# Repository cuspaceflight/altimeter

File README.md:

# CUSF Altimeter
### This project is a barebones altimeter for use in the freshers rocket challenge. The below instructions are specific to Linux systems only.

## Setting up the Repositiory

1. Setup the repository using the following commands:
```
$ git clone https://github.com/cuspaceflight/altimeter.git
$ cd altimeter
$ git submodule update --init
$ cd ChibiOS
$ git checkout stable_16.1.x
```
2. To succesfully compile firmware you will need to install gcc:
```
$ sudo apt-get install gcc-arm-none-eabi
```
3. Test the installation by compiling the firmware template:
```
$ cd ../firmware
$ make
```

## Analysing Log Files

1. Copy the file "log_0000x.bin" you wish to decode into the altimeter/logs directory

2. From the terminal run:
```
$ python3 log_file_parser.py log_0000x.bin
```

The output will print directly to the terminal window.

## Making Firmware Changes

This will be explained in depth in the sessions, however the files which you will want to modify (status.c, measurements.c and logging.c) can be found in the altimeter/firmware directory.

Compile using the command:
``` 
$ make
```
If successful something similar to the below should appear in the terminal window:

```
...
Compiling testbmk.c
Compiling main.c
Compiling ms5611.c
Compiling measure.c
Compiling status.c
Compiling microsd.c
Compiling logging.c
Linking build/altimeter.elf
Creating build/altimeter.bin
Creating build/altimeter.hex
Creating build/altimeter.dmp
Creating build/altimeter.list

   text	   data	    bss	    dec	    hex	filename
  43900	   8896	 122628	 175424	  2ad40	build/altimeter.elf

Done
```

### References

ChibiOs - http://www.chibios.org/dokuwiki/doku.php?id=chibios:documentation:start

GDB - https://github.com/blacksphere/blackmagic/wiki/Useful-GDB-commands

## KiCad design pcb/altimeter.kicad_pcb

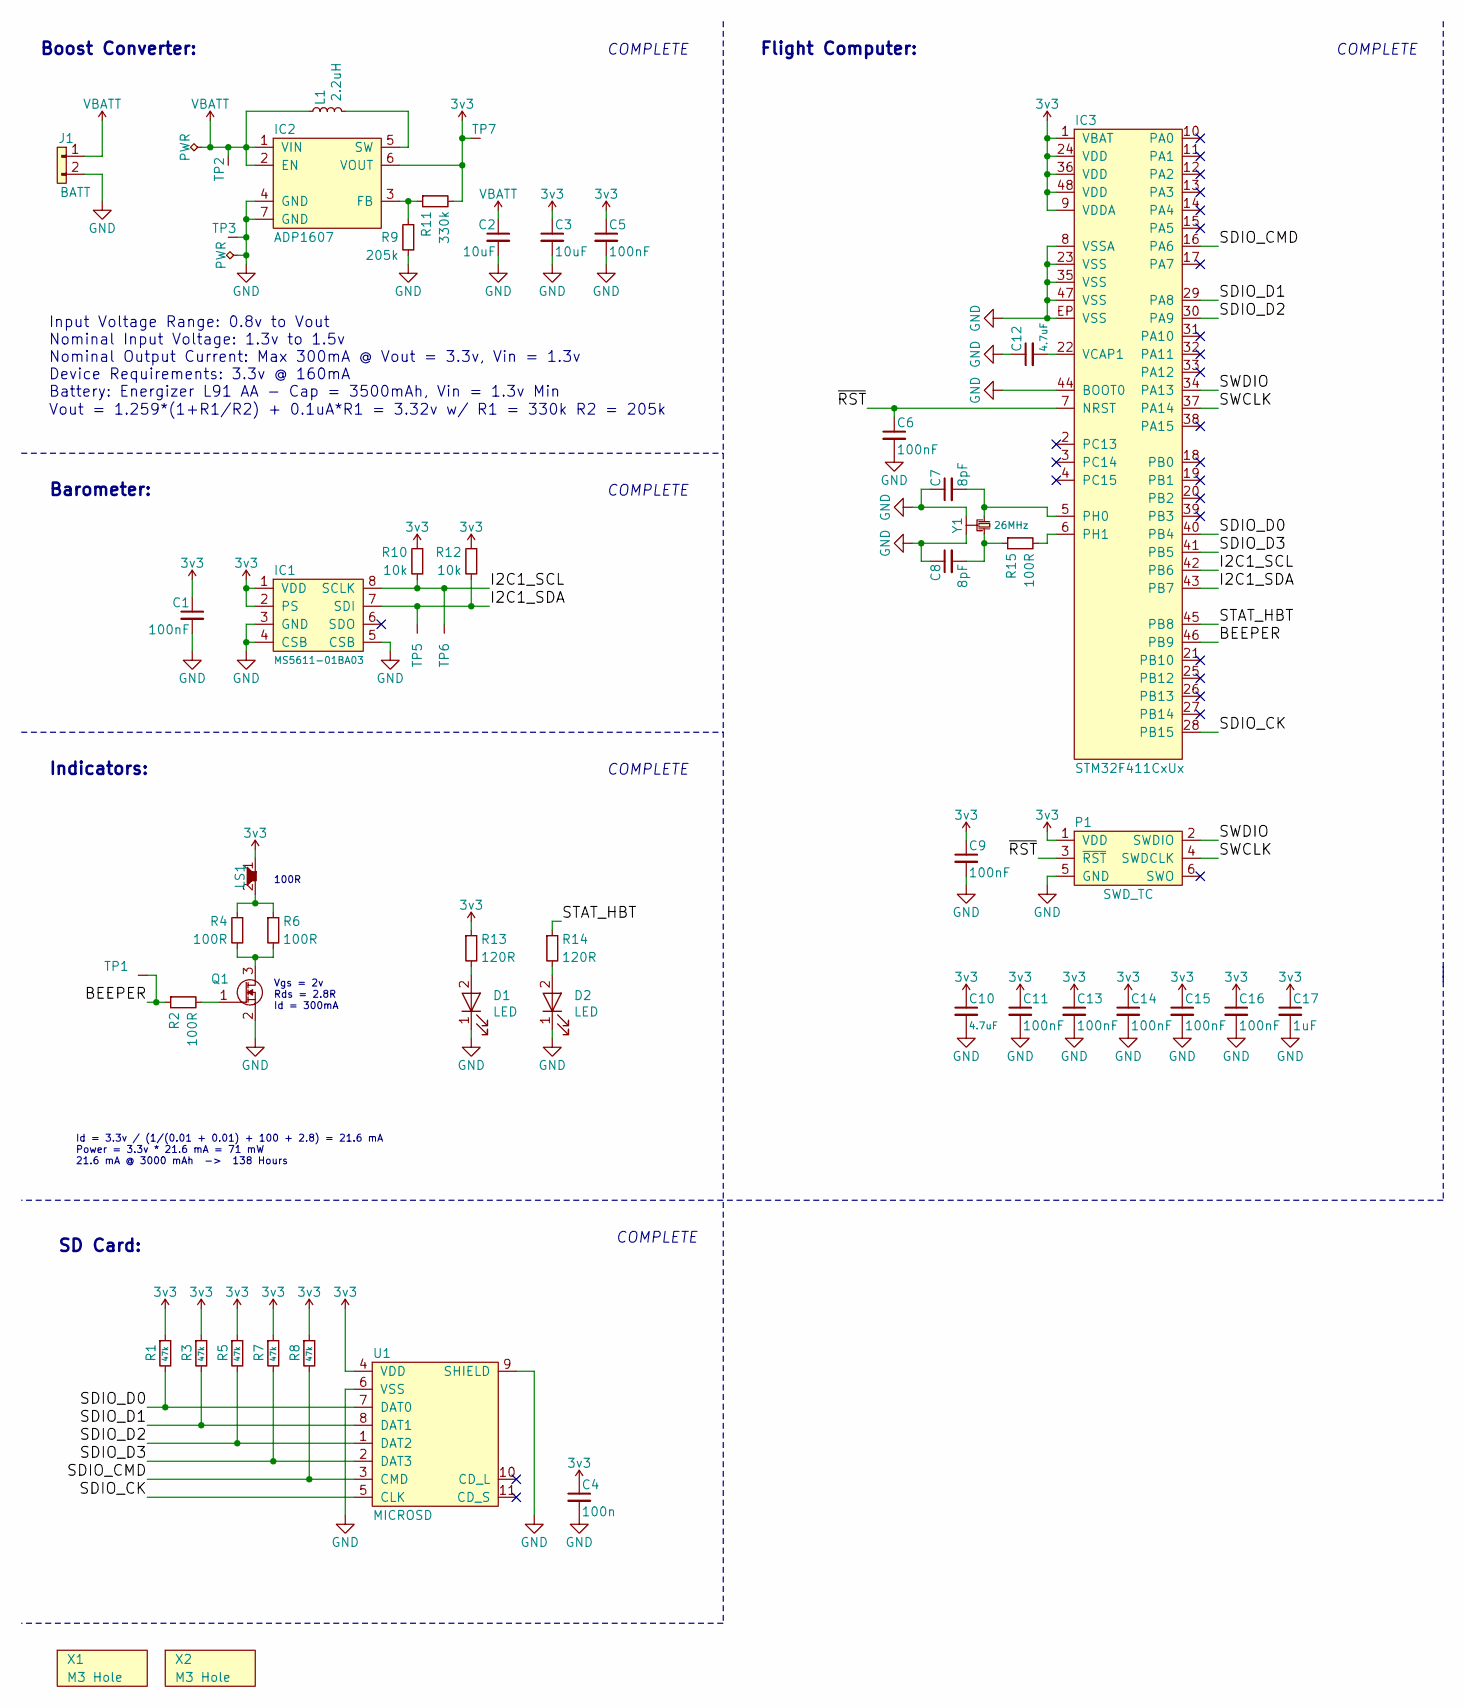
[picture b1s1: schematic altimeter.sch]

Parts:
C1, C5, C6, C9, C11, C13, C14, C15, C16: 100nF; 0402; Farnell 1828860
C2, C3: 10uF; 0805; Farnell 1657936
C4: 100n; 0603-L; Farnell 2496834
C7, C8: 8pF; 0402-L; Farnell 1758939
C10, C12: 4.7uF; 0402; Farnell 2426952
C17: 1uF; 0402; Farnell 1759381
D1, D2: LED; 0603-LED; Farnell 2290328
IC1: MS5611-01BA03; MS5611; Farnell 2362662
IC2: ADP1607; LFCSP-2x2; Farnell 2254940
IC3: STM32F411CxUx; QFN-48-EP-ST; Farnell 2456965
J1: BATT; KEYSTONE2460; Farnell 1702629
L1: 2.2uH; VLF252012MT; Farnell 2455292
LS1: SOUNDER; AI-1027-TWT-3V-R; Digikey AI-1027-TWT-3V-R
P1: SWD_TC; TC2030-NL
Q1: NFET; SOT-23; Farnell 1510761
R1, R3, R5, R7, R8: 47k; 0603-L; Farnell 9238689
R2, R4, R6: 100R; 0402; Farnell 9239111
R9: 205k; 0603-L; Farnell 2116925
R10, R12: 10k; 0402; Farnell 2072517
R11: 330k; 0603-L; Farnell 2483918
R13, R14: 120R; 0603-L; Farnell 9238379
R15: 100R; 0402-L; Farnell 2072515
TP1, TP2, TP3, TP5, TP6, TP7: TESTPAD
U1: MICROSD; MICROSD_MOLEX_503398-1892; Farnell 2358234
X1, X2: M3 Hole; M3_MOUNT
Y1: 26MHz; XTAL-20x16; Farnell 2506952

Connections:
3v3: C1.1, C3.1, C4.1, C5.1, C9.1, C10.1, C11.1, C13.1, C14.1, C15.1, C16.1, C17.1, IC1.1 (VDD), IC1.2 (PS), IC2.6 (VOUT), IC3.1 (VBAT), IC3.9 (VDDA), IC3.24 (VDD), IC3.36 (VDD), IC3.48 (VDD), LS1.1, P1.1 (VDD), R1.1, R3.1, R5.1, R7.1, R8.1, R10.1, R11.2, R12.1, R13.1, TP7.1, U1.4 (VDD)
/BEEPER: IC3.46 (PB9), R2.1, TP1.1
/I2C1_SCL: IC1.8 (SCLK), IC3.42 (PB6), R10.2, TP6.1
/I2C1_SDA: IC1.7 (SDI), IC3.43 (PB7), R12.2, TP5.1
/SDIO_CK: IC3.28 (PB15), U1.5 (CLK)
/SDIO_CMD: IC3.16 (PA6), R8.2, U1.3 (CMD)
/SDIO_D0: IC3.40 (PB4), R1.2, U1.7 (DAT0)
/SDIO_D1: IC3.29 (PA8), R3.2, U1.8 (DAT1)
/SDIO_D2: IC3.30 (PA9), R5.2, U1.1 (DAT2)
/SDIO_D3: IC3.41 (PB5), R7.2, U1.2 (DAT3)
/STAT_HBT: IC3.45 (PB8), R14.1
/SWCLK: IC3.37 (PA14), P1.4 (SWDCLK)
/SWDIO: IC3.34 (PA13), P1.2 (SWDIO)
/~RST: C6.1, IC3.7 (NRST), P1.3 (~RST)
GND: C1.2, C2.2, C3.2, C4.2, C5.2, C6.2, C7.1, C8.1, C9.2, C10.2, C11.2, C12.1, C13.2, C14.2, C15.2, C16.2, C17.2, D1.1 (K), D2.1 (K), IC1.3 (GND), IC1.4 (CSB), IC1.5 (CSB), IC2.4 (GND), IC2.7 (GND), IC3.8 (VSSA), IC3.23 (VSS), IC3.35 (VSS), IC3.44 (BOOT0), IC3.47 (VSS), IC3.EP (VSS), J1.2, P1.5 (GND), Q1.2 (S), R9.2, TP3.1, U1.6 (VSS), U1.9 (SHIELD), Y1.2, Y1.4
unnamed: C7.2, IC3.5 (PH0), Y1.1
unnamed: C8.2, R15.1, Y1.3
unnamed: C12.2, IC3.22 (VCAP1)
unnamed: D1.2 (A), R13.2
unnamed: D2.2 (A), R14.2
unnamed: IC2.3 (FB), R9.1, R11.1
unnamed: IC2.5 (SW), L1.2
unnamed: IC3.6 (PH1), R15.2
unnamed: LS1.2, R4.1, R6.1
unnamed: Q1.1 (G), R2.2
unnamed: Q1.3 (D), R4.2, R6.2
VBATT: C2.1, IC2.1 (VIN), IC2.2 (EN), J1.1, L1.1, TP2.1

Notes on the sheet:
Boost Converter:
Input Voltage Range: 0.8v to Vout Nominal Input Voltage: 1.3v to 1.5v Nominal Output Current: Max 300mA @ Vout = 3.3v, Vin = 1.3v Device Requirements: 3.3v @ 160mA Battery: Energizer L91 AA - Cap = 3500mAh, Vin = 1.3v Min
Vout = 1.259*(1+R1/R2) + 0.1uA*R1 = 3.32v w/ R1 = 330k R2 = 205k
Barometer:
Indicators:
100R
Id = 3.3v / (1/(0.01 + 0.01) + 100 + 2.8) = 21.6 mA Power = 3.3v * 21.6 mA = 71 mW 21.6 mA @ 3000 mAh -> 138 Hours
Vgs = 2v Rds = 2.8R Id = 300mA
Flight Computer:
SD Card:
COMPLETE

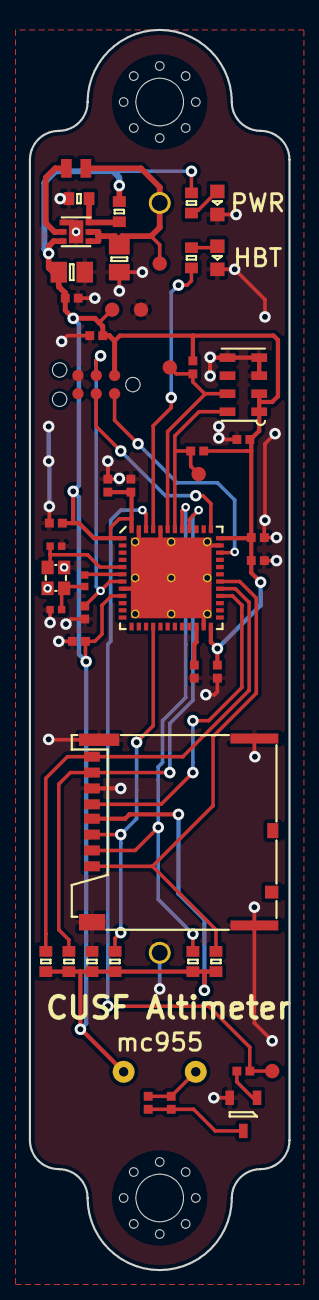
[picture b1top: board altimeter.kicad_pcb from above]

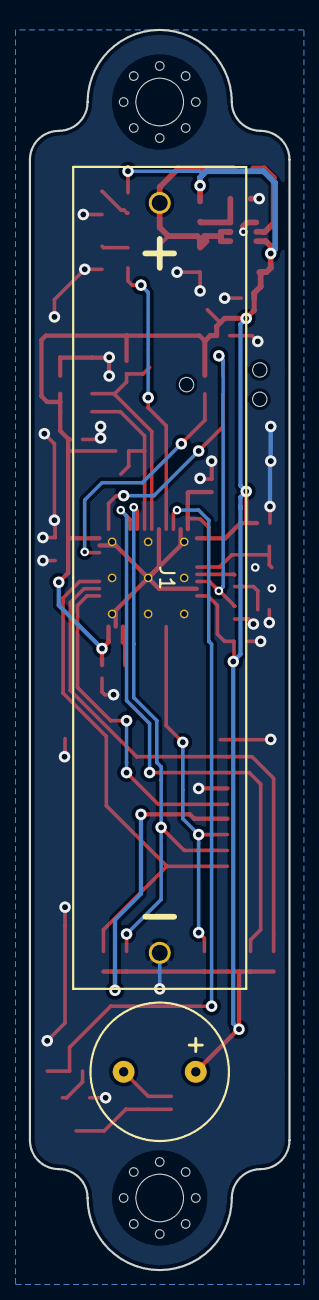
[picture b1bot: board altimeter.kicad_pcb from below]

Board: 2 copper layers, 18.0 x 86.0 mm, 52 parts (2 on the bottom side), 27 nets.

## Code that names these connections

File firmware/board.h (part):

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 * PA3  - PIN3                         (unused).
 * PA4  - PIN4                         (unused).
 * PA5  - PIN5                         (unused).
 * PA6  - SDIO_CMD                     (af12).
 * PA7  - PIN7                         (unused).
 * PA8  - SDIO_D1                      (af12).
 * PA9  - SDIO_D2                      (af12).
 * PA10 - PIN10                        (unused).
 * PA11 - PIN11                        (unused).
 * PA12 - PIN12                        (unused).
 * PA13 - SWDIO                        (af0).
 * PA14 - SWCLK                        (pulldown af0).
 * PA15 - PIN15                        (unused).
*/
#define VAL_GPIOA_MODER                (PIN_MODE_INPUT(GPIOA_PIN0) | \
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 * PB1  - PIN1                         (unused).
 * PB2  - PIN2                         (unused).
 * PB3  - PIN3                         (unused).
 * PB4  - SDIO_DO                      (af12).
 * PB5  - SDIO_D3                      (af12).
 * PB6  - I2C1_SCL                     (af4 opendrain).
 * PB7  - I2C1_SDA                     (af4 opendrain).
 * PB8  - STAT                         (output pushpull startlow).
 * PB9  - BEEP                         (output pushpull startlow pulldown).
 * PB10 - PIN10                        (unused).
 * PB11 - PIN11                        (unused).
 * PB12 - PIN12                        (unused).
 * PB13 - PIN13                        (unused).
 * PB14 - PIN14                        (unused).
 * PB15 - SDIO_CK                      (af12).
*/
#define VAL_GPIOB_MODER                (PIN_MODE_INPUT(GPIOB_PIN0) | \
                                        PIN_MODE_INPUT(GPIOB_PIN1) | \
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/*
 *  GPIOH setup:
 *
 * PH0  - PIN0                         (unused).
 * PH1  - PIN1                         (unused).
 * PH2  - PIN2                         (unused).
 * PH3  - PIN3                         (unused).
 * PH4  - PIN4                         (unused).
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
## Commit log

2017-10-11 schematic complete
2017-10-12 created board outline and placed components
2017-10-14 finished board
2017-10-26 added panel and updated bom
2017-10-30 reorganised folder
2017-10-30 added ChibiOS and started firmware
2017-10-30 removed chibios
2017-10-30 i hate submodules
2017-10-30 deleted build files
2017-10-30 added readme
2017-10-30 added microsd driver and compiled fatfs
2017-11-02 added sd card logging
2017-11-03 finished firmware template
2017-11-05 changed ChibioS to ChibiOS
2019-05-07 changed packet size to 16 bytes
2019-05-07 added plotting, need to implement filtering
2019-05-09 added filtering and subplots!
2019-05-10 updated to use barometric formula and tested parachute descent
2019-05-11 added ground level pressure
2019-05-12 flight data added

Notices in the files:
firmware/board.h:
ChibiOS - Copyright (C) 2006..2016 Giovanni Di Sirio
Licensed under the Apache License, Version 2.0 (the "License");
